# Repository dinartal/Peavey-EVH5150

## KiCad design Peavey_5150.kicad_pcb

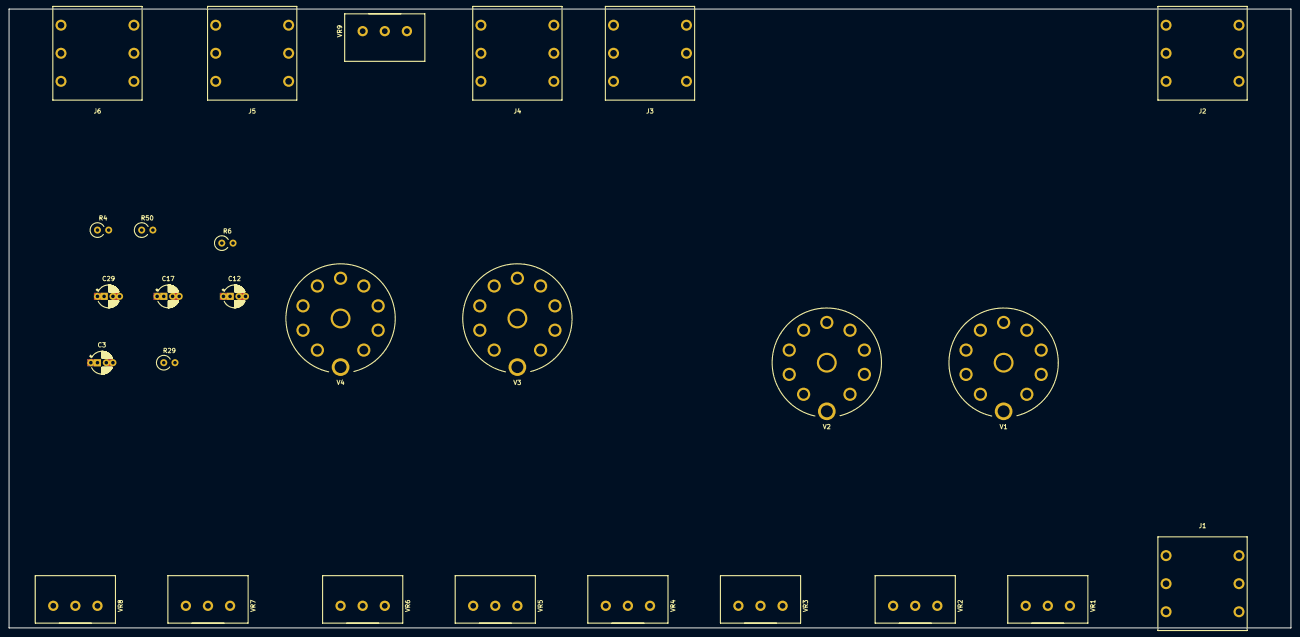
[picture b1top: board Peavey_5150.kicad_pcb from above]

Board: 2 copper layers, 290.0 x 140.0 mm, 27 parts (0 on the bottom side), 17 nets, no tracks yet.

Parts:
C3, C12, C17: 1uF 50V; KiCadCommon_CP_Vertical_MP
C29: 0.0047uF 50v; KiCadCommon_CP_Vertical_MP
J1: INPUT FRONT; KiCadCommon_Jack_Horizontal_6.35mm
J2: INPUT REAR; KiCadCommon_Jack_Horizontal_6.35mm
J3: SEND; KiCadCommon_Jack_Horizontal_6.35mm
J4: RETURN; KiCadCommon_Jack_Horizontal_6.35mm
J5: OUTPUT; KiCadCommon_Jack_Horizontal_6.35mm
J6: FOOTSWITCH; KiCadCommon_Jack_Horizontal_6.35mm
R4: 1.82K 1/2W; KiCadCommon_R_Vertical_L9.0mm_D3.2mm_P2.54mm
R6, R29: 2.2K 1/2W; KiCadCommon_R_Vertical_L9.0mm_D3.2mm_P2.54mm
R50: 3.3K 1/2W; KiCadCommon_R_Vertical_L9.0mm_D3.2mm_P2.54mm
V1, V2, V3, V4: KiCadCommon_Tube_Socket_MP
VR1, VR2, VR7, VR8: 1M LOG; KiCadCommon_Potentiometer_Alpha_Single_Horizontal
VR3, VR4: 250K; KiCadCommon_Potentiometer_Alpha_Single_Horizontal
VR5, VR9: 1M; KiCadCommon_Potentiometer_Alpha_Single_Horizontal
VR6: 25K; KiCadCommon_Potentiometer_Alpha_Single_Horizontal

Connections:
/FS1: J6.3, J6.4
/FS2: J6.1, J6.2
/HEAT+: V1.4, V2.4, V3.4, V4.4
Earth: C3.2, C12.2, C17.2, J1.3, J1.4, J1.5, J1.6, J2.2, J2.3, J2.4, J2.5, J2.6, R4.1, R29.1, VR1.1, VR2.1
Earth_Protective: C29.2, J3.3, J3.4, J3.5, J3.6, J4.3, J4.4, J4.5, J4.6, J5.3, J5.4, J5.5, J5.6, R50.1, VR6.1, VR7.1, VR8.1, VR9.1
GND: J6.5, J6.6, V1.5, V2.5, V3.5, V4.5
unnamed: C3.1, R4.2, V1.8
unnamed: C12.1, V1.3
unnamed: C17.1, V2.3
unnamed: VR3.2, VR3.3
unnamed: VR4.1, VR5.2, VR5.3
unnamed: C29.1, R50.2, V4.3
unnamed: J3.1, J3.2, J4.2
unnamed: J5.1, J5.2, VR9.3
unnamed: R29.2, V3.3
unnamed: VR4.3, VR7.2, VR8.2
unnamed: VR5.1, VR6.2

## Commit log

2020-05-27 First add
2020-05-27 Working on schematic
2020-05-27 finish
2020-05-27 add led
2020-06-13 Some values fixed
2020-06-24 Input changes
2020-09-26 add components
2020-09-27 add schematic
2020-09-28 add cap models
2020-09-28 change d to 1.2mm
2020-09-29 add some r watts
2020-09-29 add watts to R
2020-10-17 add MKP cap
2020-10-31 add some parts to lib
2020-11-04 Universal Capacitors Footprints
2020-11-12 Footprint partial assignment
2020-11-12 Footprint update
2020-11-14 add relays
2020-11-26 add models
2020-11-26 3d model path fix
2020-11-26 Connector footprint
2020-11-26 CP Uneversal 3d
2020-11-26 add 3D
2020-11-30 return schematic to last valid
2020-12-18 Wattage and voltage corrections
2021-04-03 gitignore
2021-04-03 Common library as a submodule
2021-04-20 move rescue lib
2021-04-28 relaative path
2021-04-28 Removed cache files
2021-04-28 Common Lib
2021-04-28 Prettify
2021-04-28 ignore
2021-04-28 Clenup / footprint assignment
2021-04-29 Removed project library
2021-04-29 Annotation
2021-04-29 Some footprints assigned
2021-05-02 Initial Markup
2021-05-02 Thinking...
